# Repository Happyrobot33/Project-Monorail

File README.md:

# Project-Monorail
Project Monorail is an attempt to recreate a design shown by Nicholas Seward (https://www.youtube.com/watch?v=oBBhVcemVHc&amp;t=26s) that uses 1 linear rail to accomplish 3 dimensional movement

Use this to visualize if a point is reachable or not to prevent issues:
https://editor.p5js.org/Happyrobot33/sketches/HqeGeLe6U

https://user-images.githubusercontent.com/32679887/117662900-11516d00-b16e-11eb-9a66-542f85682d6e.mp4

https://user-images.githubusercontent.com/32679887/118267545-3d306380-b48a-11eb-8856-cf8bc8f9db5a.mp4

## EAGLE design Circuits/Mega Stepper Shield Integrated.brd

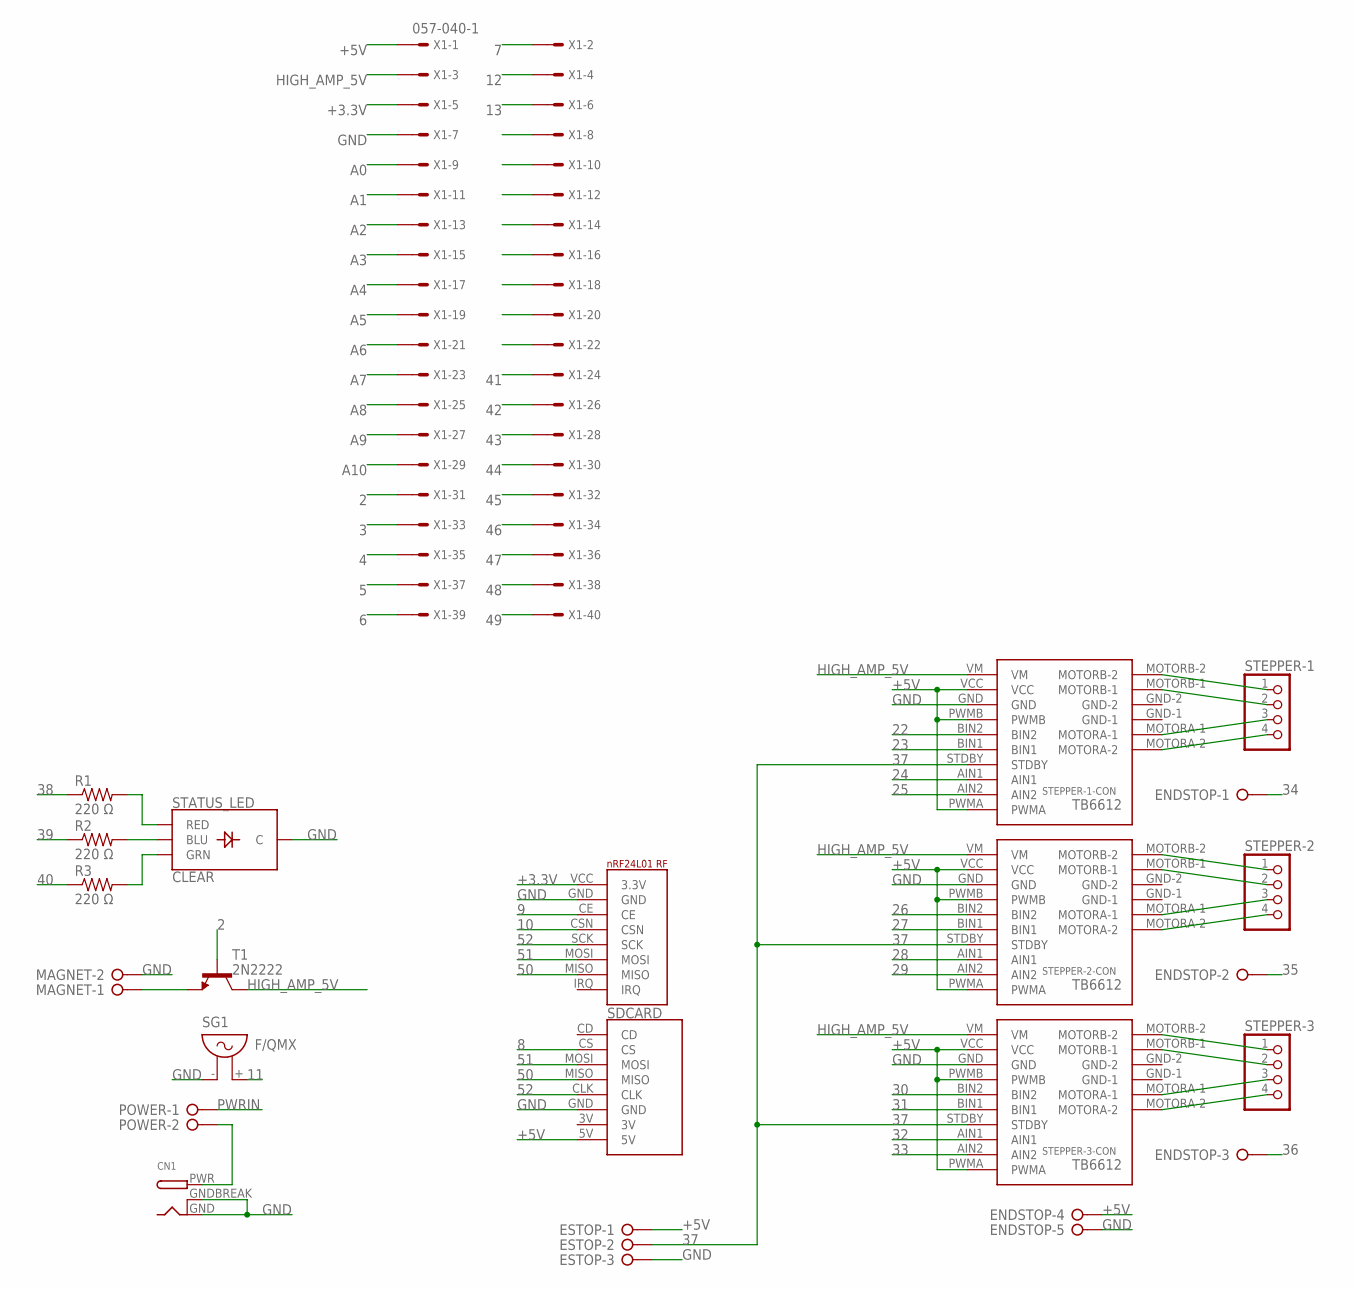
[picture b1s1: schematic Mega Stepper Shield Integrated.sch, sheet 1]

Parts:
CN1: DCBARRELPTH; DCJACK_2MM_PTH
ENDSTOP: W237-05P; W237-5P
ESTOP: W237-3E
MAGNET: W237-02P; W237-132
POWER: W237-02P; W237-132
R1, R2, R3: 220 Ω; 0204/7
SDCARD: MICRO_SD_BREAKOUT; MICROSDCARDBREAKOUT
SG1: F/QMX
STATUS_LED: CLEAR; LED-RGB-THRU
STEPPER-1, STEPPER-2, STEPPER-3: PINHD-1X4; 1X04
STEPPER-1-CON, STEPPER-2-CON, STEPPER-3-CON: TB6612-BREAKOUT-MOTOR-CONTROLLER; TB6612-HEADERS
T1: 2N2222; TO92-EBC-OVAL
U$1: NRF24L01_RF_MODULE; NRF24L01RF
X1: 057-040-1

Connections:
2: T1.B, X1.31; also elsewhere on the board
3: X1.33; also elsewhere on the board
4: X1.35; also elsewhere on the board
5: X1.37; also elsewhere on the board
6: X1.39; also elsewhere on the board
7: X1.2; also elsewhere on the board
8: SDCARD.CS; also elsewhere on the board
9: U$1.CE; also elsewhere on the board
10: U$1.CSN; also elsewhere on the board
11: SG1.+ (2); also elsewhere on the board
12: X1.4; also elsewhere on the board
13: X1.6; also elsewhere on the board
16: X1.8
22: STEPPER-1-CON.BIN2; also elsewhere on the board
23: STEPPER-1-CON.BIN1; also elsewhere on the board
24: STEPPER-1-CON.AIN1; also elsewhere on the board
25: STEPPER-1-CON.AIN2; also elsewhere on the board
26: STEPPER-2-CON.BIN2; also elsewhere on the board
27: STEPPER-2-CON.BIN1; also elsewhere on the board
28: STEPPER-2-CON.AIN1; also elsewhere on the board
29: STEPPER-2-CON.AIN2; also elsewhere on the board
30: STEPPER-3-CON.BIN2; also elsewhere on the board
31: STEPPER-3-CON.BIN1; also elsewhere on the board
32: STEPPER-3-CON.AIN1; also elsewhere on the board
33: STEPPER-3-CON.AIN2; also elsewhere on the board
34: ENDSTOP.1; also elsewhere on the board
35: ENDSTOP.2; also elsewhere on the board
36: ENDSTOP.3; also elsewhere on the board
37: ESTOP.2, STEPPER-1-CON.STDBY, STEPPER-2-CON.STDBY, STEPPER-3-CON.STDBY; also elsewhere on the board
38: R1.1; also elsewhere on the board
39: R2.1; also elsewhere on the board
40: R3.1, X1.22; also elsewhere on the board
41: X1.24; also elsewhere on the board
42: X1.26; also elsewhere on the board
43: X1.28; also elsewhere on the board
44: X1.30; also elsewhere on the board
45: X1.32; also elsewhere on the board
46: X1.34; also elsewhere on the board
47: X1.36; also elsewhere on the board
48: X1.38; also elsewhere on the board
49: X1.40; also elsewhere on the board
50: SDCARD.MISO, U$1.MISO; also elsewhere on the board
51: SDCARD.MOSI, U$1.MOSI; also elsewhere on the board
52: SDCARD.CLK, U$1.SCK; also elsewhere on the board
+3.3V: U$1.VCC (3.3V), X1.5
+5V: ENDSTOP.4, ESTOP.1, SDCARD.5V, STEPPER-1-CON.PWMA, STEPPER-1-CON.PWMB, STEPPER-1-CON.VCC, STEPPER-2-CON.PWMA, STEPPER-2-CON.PWMB, STEPPER-2-CON.VCC, STEPPER-3-CON.PWMA, STEPPER-3-CON.PWMB, STEPPER-3-CON.VCC, X1.1; also elsewhere on the board
A0: X1.9; also elsewhere on the board
A1: X1.11; also elsewhere on the board
A2: X1.13; also elsewhere on the board
A3: X1.15; also elsewhere on the board
A4: X1.17; also elsewhere on the board
A5: X1.19; also elsewhere on the board
A6: X1.21; also elsewhere on the board
A7: X1.23; also elsewhere on the board
A8: X1.25; also elsewhere on the board
A9: X1.27; also elsewhere on the board
A10: X1.29; also elsewhere on the board
GND: CN1.GND, CN1.GNDBREAK, ENDSTOP.5, ESTOP.3, MAGNET.2, SDCARD.GND, SG1.- (1), STATUS_LED.2 (C), STEPPER-1-CON.GND, STEPPER-2-CON.GND, STEPPER-3-CON.GND, U$1.GND, X1.7; also elsewhere on the board
HIGH_AMP_5V: STEPPER-1-CON.VM, STEPPER-2-CON.VM, STEPPER-3-CON.VM, T1.C, X1.3; also elsewhere on the board
unnamed: CN1.PWR, POWER.2
unnamed: STEPPER-1.1, STEPPER-1-CON.MOTORB-2
unnamed: STEPPER-1.2, STEPPER-1-CON.MOTORB-1
unnamed: STEPPER-1.3, STEPPER-1-CON.MOTORA-1
unnamed: STEPPER-1.4, STEPPER-1-CON.MOTORA-2
unnamed: STEPPER-2.1, STEPPER-2-CON.MOTORB-2
unnamed: STEPPER-2.2, STEPPER-2-CON.MOTORB-1
unnamed: STEPPER-2.3, STEPPER-2-CON.MOTORA-1
unnamed: STEPPER-2.4, STEPPER-2-CON.MOTORA-2
unnamed: STEPPER-3.1, STEPPER-3-CON.MOTORB-2
unnamed: STEPPER-3.2, STEPPER-3-CON.MOTORB-1
unnamed: STEPPER-3.3, STEPPER-3-CON.MOTORA-1
unnamed: STEPPER-3.4, STEPPER-3-CON.MOTORA-2
unnamed: R3.2, STATUS_LED.3 (GRN)
unnamed: R2.2, STATUS_LED.4 (BLU)
unnamed: R1.2, STATUS_LED.1 (RED)
unnamed: MAGNET.1, T1.E
PWRIN: POWER.1; also elsewhere on the board

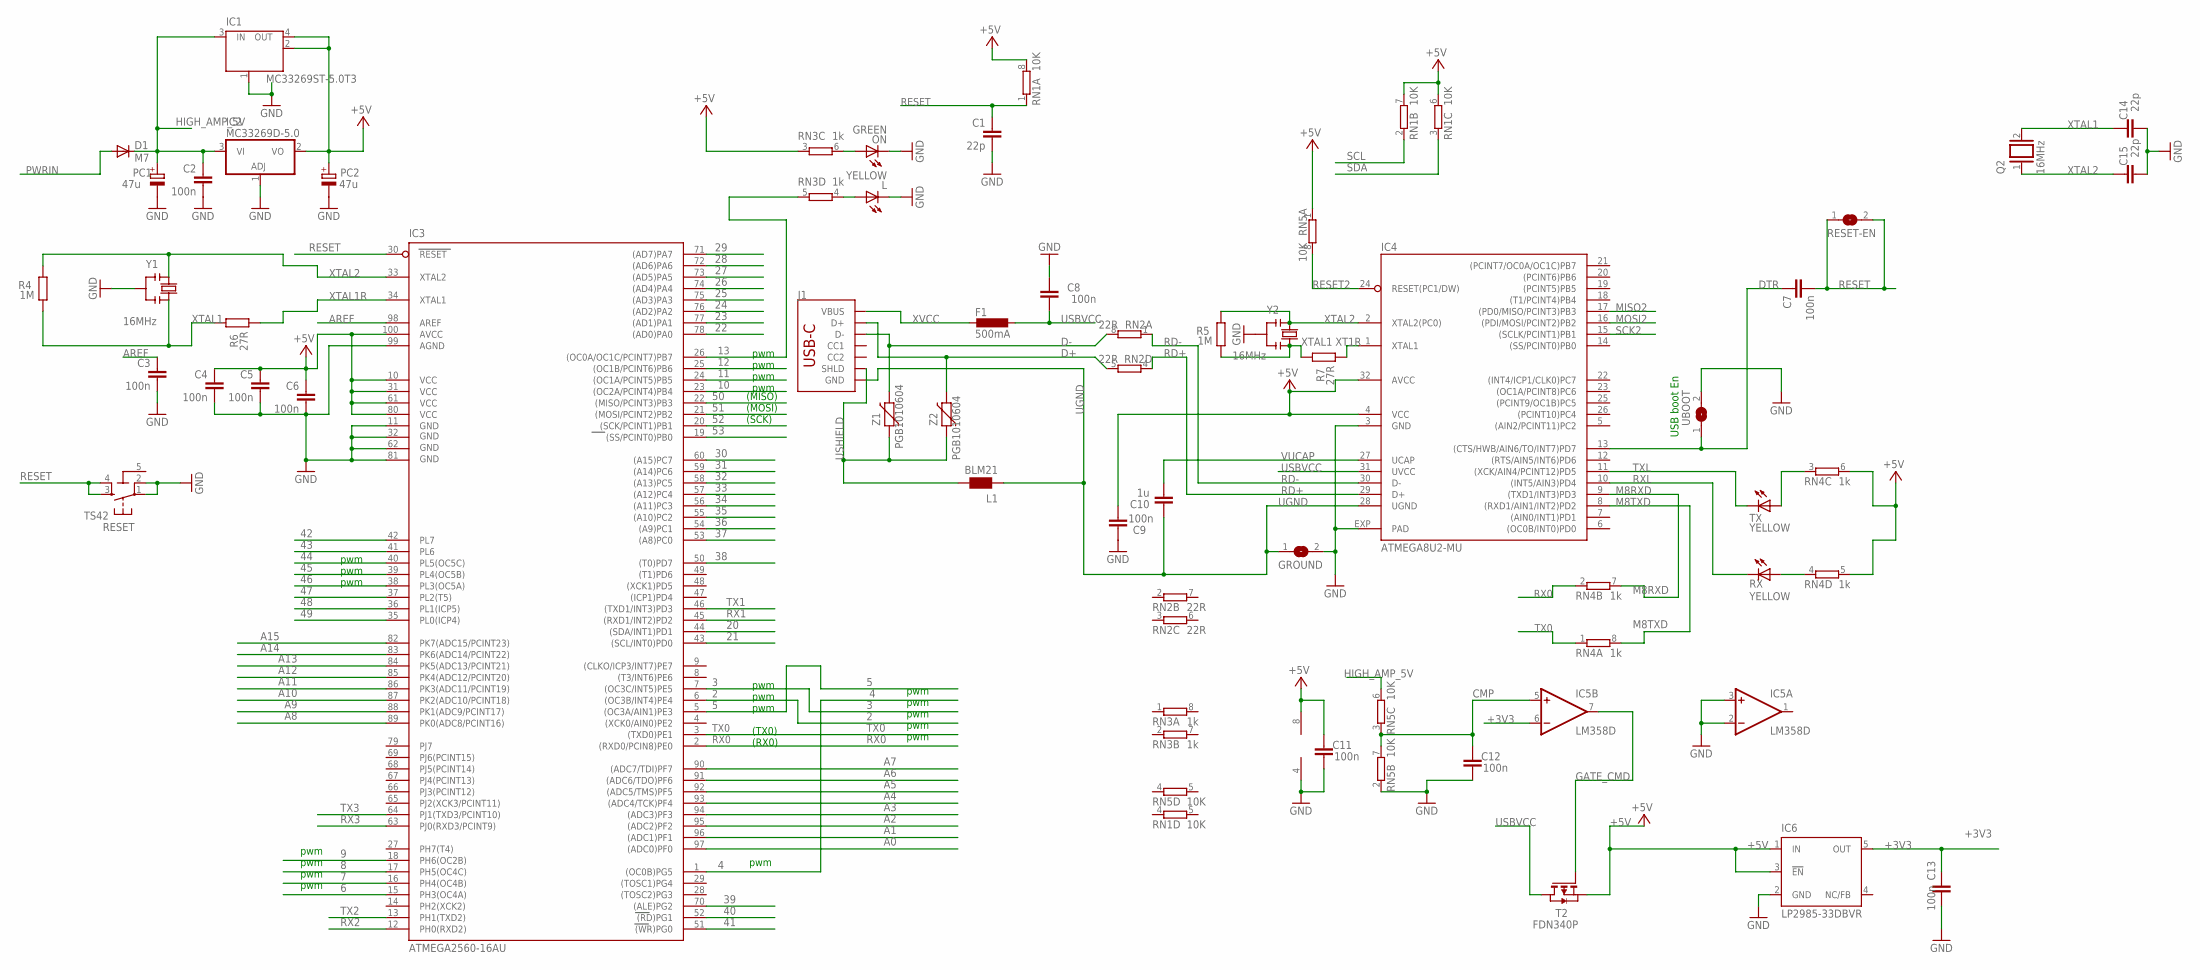
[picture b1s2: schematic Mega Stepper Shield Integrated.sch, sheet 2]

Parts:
C1, C14, C15: 22p; C0603-ROUND
C2, C3, C4, C5, C6, C7, C9, C12, C13: 100n; C0603-ROUND
C8, C11: 100n; C0603
C10: 1u; C0603-ROUND
D1: M7; SMB
F1: 500mA; L1812
GROUND: SJ
IC1: MC33269ST-5.0T3; SOT223
IC2: MC33269D-5.0; DPACK
IC3: ATMEGA2560-16AU; TQFP100
IC4: ATMEGA8U2-MU; QFN32
IC5: LM358D; SO08
IC6: LP2985-33DBVR; SOT23-DBV
J1: USB_C_2-LAYER_PADS; USB-C-16P-2LAYER-PADS
L: YELLOW; CHIP-LED0805
L1: BLM21; 0805
ON: GREEN; CHIP-LED0805
PC1, PC2: 47u; PANASONIC_D
Q2: 16MHz; QS
R4, R5: 1M; R0603-ROUND
R6, R7: 27R; R0603-ROUND
RESET: TS42
RESET-EN: SJ
RN1, RN5: 10K; CAT16
RN2: 22R; CAY16
RN3, RN4: 1k; CAY16
RX: YELLOW; CHIP-LED0805
T2: FDN340P; SOT-23
TX: YELLOW; CHIP-LED0805
UBOOT: SJ
Y1, Y2: 16MHz; RESONATOR
Z1, Z2: PGB1010604; CT/CN0603

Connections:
2: IC3.6 ((OC3B/INT4)PE4); also elsewhere on the board
3: IC3.7 ((OC3C/INT5)PE5); also elsewhere on the board
4: IC3.1 ((OC0B)PG5); also elsewhere on the board
5: IC3.5 ((OC3A/AIN1)PE3); also elsewhere on the board
5-GND: RESET.5 (5-GND)
6: IC3.15 (PH3(OC4A)); also elsewhere on the board
7: IC3.16 (PH4(OC4B)); also elsewhere on the board
8: IC3.17 (PH5(OC4C)); also elsewhere on the board
9: IC3.18 (PH6(OC2B)); also elsewhere on the board
10: IC3.23 ((OC2A/PCINT4)PB4); also elsewhere on the board
11: IC3.24 ((OC1A/PCINT5)PB5); also elsewhere on the board
12: IC3.25 ((OC1B/PCINT6)PB6); also elsewhere on the board
13: IC3.26 ((OC0A/OC1C/PCINT7)PB7), RN3.5 (2); also elsewhere on the board
20: IC3.44 ((SDA/INT1)PD1)
21: IC3.43 ((SCL/INT0)PD0)
22: IC3.78 ((AD0)PA0); also elsewhere on the board
23: IC3.77 ((AD1)PA1); also elsewhere on the board
24: IC3.76 ((AD2)PA2); also elsewhere on the board
25: IC3.75 ((AD3)PA3); also elsewhere on the board
26: IC3.74 ((AD4)PA4); also elsewhere on the board
27: IC3.73 ((AD5)PA5); also elsewhere on the board
28: IC3.72 ((AD6)PA6); also elsewhere on the board
29: IC3.71 ((AD7)PA7); also elsewhere on the board
30: IC3.60 ((A15)PC7); also elsewhere on the board
31: IC3.59 ((A14)PC6); also elsewhere on the board
32: IC3.58 ((A13)PC5); also elsewhere on the board
33: IC3.57 ((A12)PC4); also elsewhere on the board
34: IC3.56 ((A11)PC3); also elsewhere on the board
35: IC3.55 ((A10)PC2); also elsewhere on the board
36: IC3.54 ((A9)PC1); also elsewhere on the board
37: IC3.53 ((A8)PC0); also elsewhere on the board
38: IC3.50 ((T0)PD7); also elsewhere on the board
39: IC3.70 ((ALE)PG2); also elsewhere on the board
40: IC3.52 ((RD)PG1); also elsewhere on the board
41: IC3.51 ((WR)PG0); also elsewhere on the board
42: IC3.42 (PL7); also elsewhere on the board
43: IC3.41 (PL6); also elsewhere on the board
44: IC3.40 (PL5(OC5C)); also elsewhere on the board
45: IC3.39 (PL4(OC5B)); also elsewhere on the board
46: IC3.38 (PL3(OC5A)); also elsewhere on the board
47: IC3.37 (PL2(T5)); also elsewhere on the board
48: IC3.36 (PL1(ICP5)); also elsewhere on the board
49: IC3.35 (PL0(ICP4)); also elsewhere on the board
50: IC3.22 ((MISO/PCINT3)PB3); also elsewhere on the board
51: IC3.21 ((MOSI/PCINT2)PB2); also elsewhere on the board
52: IC3.20 ((SCK/PCINT1)PB1); also elsewhere on the board
53: IC3.19 ((SS/PCINT0)PB0)
+3V3: C13.2, IC5.6 (-IN), IC6.5 (OUT)
+5V: C4.1, C5.1, C6.1, C9.1, C11.2, IC1.2 (OUT), IC1.4 (OUT), IC2.2 (VO), IC3.10 (VCC), IC3.31 (VCC1), IC3.61 (VCC2), IC3.80 (VCC3), IC3.100 (AVCC), IC4.4 (VCC), IC4.32 (AVCC), IC5.8 (V+), IC6.1 (IN), IC6.3 (!EN), PC2.+, RN1.6 (2), RN1.7 (2), RN1.8 (2), RN3.3 (1), RN4.5 (2), RN4.6 (2), RN5.1, T2.2 (S); also elsewhere on the board
A0: IC3.97 ((ADC0)PF0); also elsewhere on the board
A1: IC3.96 ((ADC1)PF1); also elsewhere on the board
A2: IC3.95 ((ADC2)PF2); also elsewhere on the board
A3: IC3.94 ((ADC3)PF3); also elsewhere on the board
A4: IC3.93 ((ADC4/TCK)PF4); also elsewhere on the board
A5: IC3.92 ((ADC5/TMS)PF5); also elsewhere on the board
A6: IC3.91 ((ADC6/TDO)PF6); also elsewhere on the board
A7: IC3.90 ((ADC7/TDI)PF7); also elsewhere on the board
A8: IC3.89 (PK0(ADC8/PCINT16)); also elsewhere on the board
A9: IC3.88 (PK1(ADC9/PCINT17)); also elsewhere on the board
A10: IC3.87 (PK2(ADC10/PCINT18)); also elsewhere on the board
A11: IC3.86 (PK3(ADC11/PCINT19))
A12: IC3.85 (PK4(ADC12/PCINT20))
A13: IC3.84 (PK5(ADC13/PCINT21))
A14: IC3.83 (PK6(ADC14/PCINT22))
A15: IC3.82 (PK7(ADC15/PCINT23))
AREF: C3.1, IC3.98 (AREF)
CMP: C12.2, IC5.5 (+IN), RN5.3 (1), RN5.7 (2)
D+: J1.A6 (D+), J1.B6 (D+), RN2.5 (2), Z2.2
D-: J1.A7 (D-), J1.B7 (D-), RN2.8 (2), Z1.2
DTR: C7.1, IC4.13 ((CTS/HWB/AIN6/TO/INT7)PD7), UBOOT.1
GATE_CMD: IC5.7 (OUT), T2.3 (G)
GND: C1.2, C2.2, C3.2, C4.2, C5.2, C6.2, C8.2, C9.2, C11.1, C12.1, C13.1, C14.1, C15.1, GROUND.2, IC1.1 (GND/ADJ), IC2.1 (ADJ), IC3.11 (GND), IC3.32 (GND1), IC3.62 (GND2), IC3.81 (GND3), IC3.99 (AGND), IC4.3 (GND), IC4.EXP (PAD), IC5.2 (-IN), IC5.3 (+IN), IC5.4 (V-), IC6.2 (GND), L.C, ON.C, PC1.-, PC2.-, RESET.1, RESET.2, RN5.2 (1), UBOOT.2, Y1.2, Y2.2; also elsewhere on the board
HIGH_AMP_5V: C2.1, D1.C, IC1.3 (IN), IC2.3 (VI), PC1.+, RN5.6 (2); also elsewhere on the board
M8RXD: IC4.9 ((TXD1/INT3)PD3), RN4.7 (2)
M8TXD: IC4.8 ((RXD1/AIN1/INT2)PD2), RN4.8 (2)
MISO2: IC4.17 ((PD0/MISO/PCINT3)PB3)
MOSI2: IC4.16 ((PDI/MOSI/PCINT2)PB2)
unnamed: ON.A, RN3.6 (2)
unnamed: L.A, RN3.4 (1)
unnamed: RN4.4 (1), RX.A
unnamed: RN4.3 (1), TX.A
PWRIN: D1.A; also elsewhere on the board
RD+: IC4.29 (D+), RN2.4 (1)
RD-: IC4.30 (D-), RN2.1
RESET: C1.1, C7.2, IC3.30 (RESET), RESET.3, RESET.4, RESET-EN.1, RESET-EN.2, RN1.1
RESET2: IC4.24 (RESET(PC1/DW)), RN5.8 (2)
RX0: IC3.2 ((RXD0/PCIN8)PE0), RN4.2 (1)
RX1: IC3.45 ((RXD1/INT2)PD2)
RX2: IC3.12 (PH0(RXD2))
RX3: IC3.63 (PJ0(RXD3/PCINT9))
RXL: IC4.10 ((INT5/AIN3)PD4), RX.C
SCK2: IC4.15 ((SCLK/PCINT1)PB1)
SCL: RN1.2 (1)
SDA: RN1.3 (1)
TX0: IC3.3 ((TXD0)PE1), RN4.1
TX1: IC3.46 ((TXD1/INT3)PD3)
TX2: IC3.13 (PH1(TXD2))
TX3: IC3.64 (PJ1(TXD3/PCINT10))
TXL: IC4.11 ((XCK/AIN4/PCINT12)PD5), TX.C
UGND: C10.2, GROUND.1, IC4.28 (UGND), J1.GND, J1.GND2 (GND), L1.1
USBVCC: C8.1, F1.1, IC4.31 (UVCC), T2.1 (D)
USHIELD: J1.SHLD1 (SHLD), J1.SHLD2 (SHLD), J1.SHLD3 (SHLD), J1.SHLD4 (SHLD), L1.2, Z1.1, Z2.1
VUCAP: C10.1, IC4.27 (UCAP)
XT1R: IC4.1 (XTAL1), R7.1
XTAL1: C14.2, Q2.2, R4.1, R5.1, R6.2, R7.2, Y1.3, Y2.3
XTAL1R: IC3.34 (XTAL1), R6.1
XTAL2: C15.2, IC3.33 (XTAL2), IC4.2 (XTAL2(PC0)), Q2.1, R4.2, R5.2, Y1.1, Y2.1
XVCC: F1.2, J1.VBUS1 (VBUS), J1.VBUS2 (VBUS)

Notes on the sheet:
pwm
(TX0)
(RX0)
(MISO)
(SCK)
(MOSI)
USB boot En

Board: 2 copper layers, 70 parts (0 on the bottom side), 106 nets, no tracks yet.

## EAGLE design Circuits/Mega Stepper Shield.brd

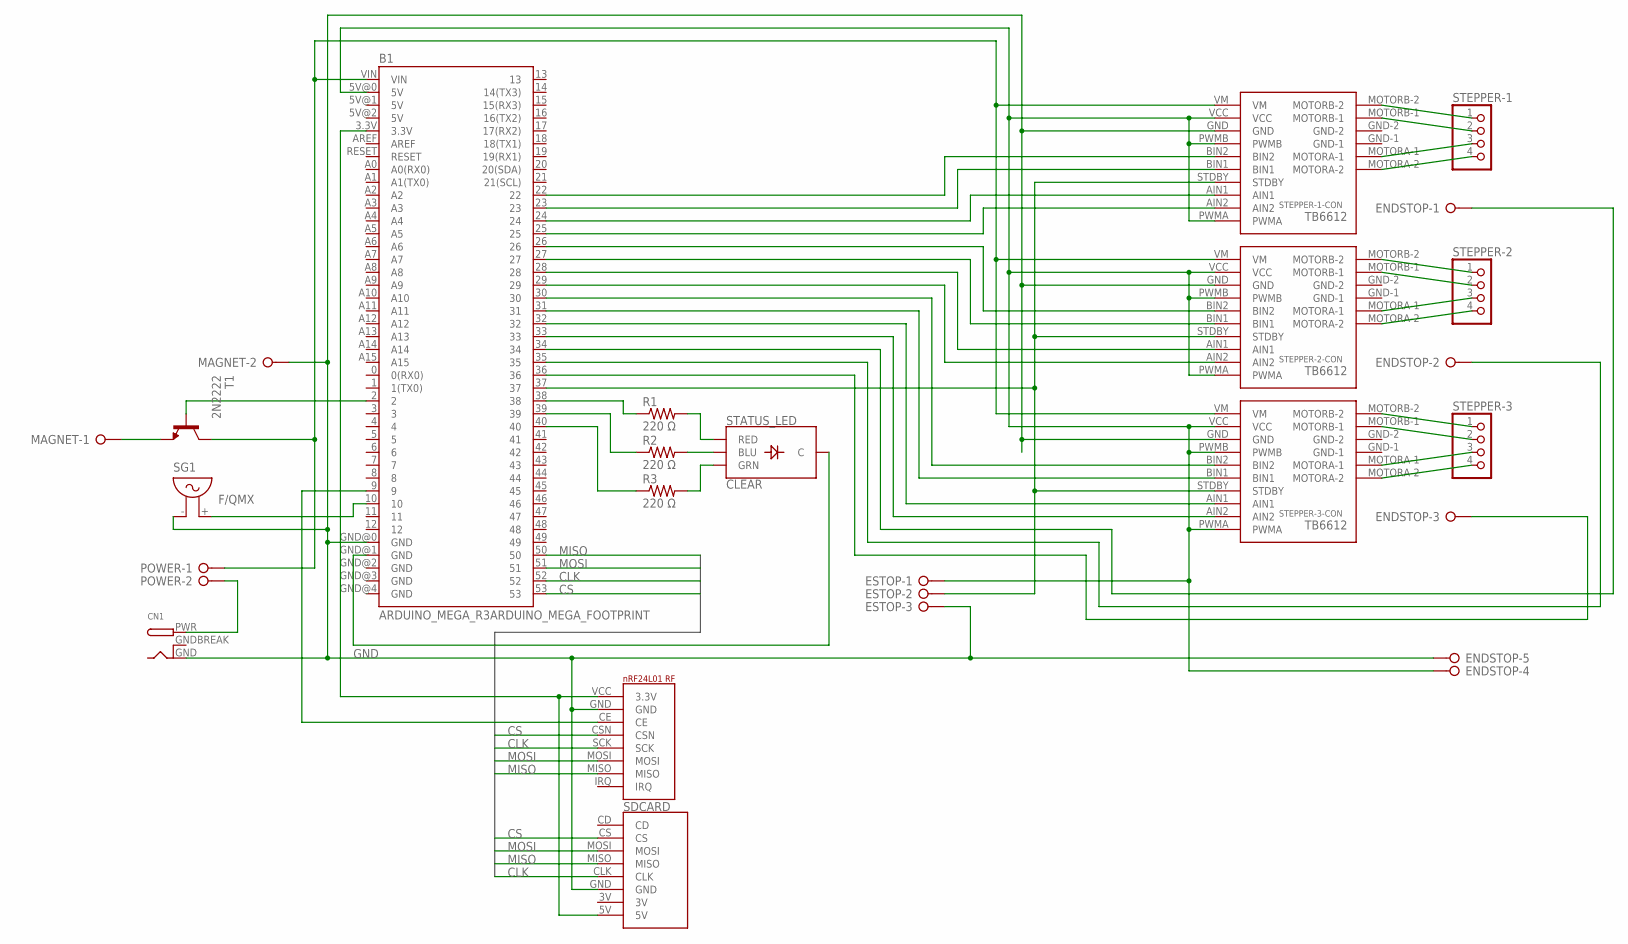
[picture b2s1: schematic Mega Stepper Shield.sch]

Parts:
B1: ARDUINO_MEGA_R3ARDUINO_MEGA_FOOTPRINT; ARDUINO_MEGA_SHIELD_DIMENSIONLESS
CN1: DCBARRELPTH; DCJACK_2MM_PTH
ENDSTOP: W237-05P; W237-5P
ESTOP: W237-3E
MAGNET: W237-02P; W237-132
POWER: W237-02P; W237-132
R1, R2, R3: 220 Ω; 0204/7
SDCARD: MICRO_SD_BREAKOUT; MICROSDCARDBREAKOUT
SG1: F/QMX
STATUS_LED: CLEAR; LED-RGB-THRU
STEPPER-1, STEPPER-2, STEPPER-3: PINHD-1X4; 1X04
STEPPER-1-CON, STEPPER-2-CON, STEPPER-3-CON: TB6612-BREAKOUT-MOTOR-CONTROLLER; TB6612-HEADERS
T1: 2N2222; TO92-EBC-OVAL
U$1: NRF24L01_RF_MODULE; NRF24L01RF

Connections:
3.3V: B1.3.3V, SDCARD.5V, U$1.VCC (3.3V)
5V: B1.5V@0 (5V), ENDSTOP.4, ESTOP.1, STEPPER-1-CON.PWMA, STEPPER-1-CON.PWMB, STEPPER-1-CON.VCC, STEPPER-2-CON.PWMA, STEPPER-2-CON.PWMB, STEPPER-2-CON.VCC, STEPPER-3-CON.PWMA, STEPPER-3-CON.PWMB, STEPPER-3-CON.VCC
12V10A: B1.VIN, POWER.1, STEPPER-1-CON.VM, STEPPER-2-CON.VM, STEPPER-3-CON.VM, T1.C
AIN1: B1.24, STEPPER-1-CON.AIN1
AIN2: B1.25, STEPPER-1-CON.AIN2
BIN2: B1.22, STEPPER-1-CON.BIN2
CLK: B1.52, SDCARD.CLK, U$1.SCK
CS: B1.53, SDCARD.CS, U$1.CSN
GND: B1.GND@0 (GND), CN1.GND, ENDSTOP.5, ESTOP.3, MAGNET.2, SDCARD.GND, SG1.- (1), STEPPER-1-CON.GND, STEPPER-2-CON.GND, STEPPER-3-CON.GND, U$1.GND
GNDBREAK: CN1.GNDBREAK
MISO: B1.50, SDCARD.MISO, U$1.MISO
MOSI: B1.51, SDCARD.MOSI, U$1.MOSI
unnamed: B1.36, ENDSTOP.3
unnamed: B1.10, SG1.+ (2)
unnamed: B1.30, STEPPER-3-CON.BIN2
unnamed: B1.26, STEPPER-2-CON.BIN2
unnamed: B1.27, STEPPER-2-CON.BIN1
unnamed: B1.28, STEPPER-2-CON.AIN1
unnamed: B1.29, STEPPER-2-CON.AIN2
unnamed: B1.31, STEPPER-3-CON.BIN1
unnamed: B1.32, STEPPER-3-CON.AIN1
unnamed: B1.33, STEPPER-3-CON.AIN2
unnamed: CN1.PWR, POWER.2
unnamed: B1.35, ENDSTOP.2
unnamed: B1.37, ESTOP.2, STEPPER-1-CON.STDBY, STEPPER-2-CON.STDBY, STEPPER-3-CON.STDBY
unnamed: B1.34, ENDSTOP.1
unnamed: STEPPER-1.1, STEPPER-1-CON.MOTORB-2
unnamed: STEPPER-1.2, STEPPER-1-CON.MOTORB-1
unnamed: STEPPER-1.3, STEPPER-1-CON.MOTORA-1
unnamed: STEPPER-1.4, STEPPER-1-CON.MOTORA-2
unnamed: STEPPER-2.1, STEPPER-2-CON.MOTORB-2
unnamed: STEPPER-2.2, STEPPER-2-CON.MOTORB-1
unnamed: STEPPER-2.3, STEPPER-2-CON.MOTORA-1
unnamed: STEPPER-2.4, STEPPER-2-CON.MOTORA-2
unnamed: STEPPER-3.1, STEPPER-3-CON.MOTORB-2
unnamed: STEPPER-3.2, STEPPER-3-CON.MOTORB-1
unnamed: STEPPER-3.3, STEPPER-3-CON.MOTORA-1
unnamed: STEPPER-3.4, STEPPER-3-CON.MOTORA-2
unnamed: B1.23, STEPPER-1-CON.BIN1
unnamed: R3.2, STATUS_LED.3 (GRN)
unnamed: R2.2, STATUS_LED.4 (BLU)
unnamed: R1.2, STATUS_LED.1 (RED)
unnamed: B1.GND@1 (GND), STATUS_LED.2 (C)
unnamed: B1.9, U$1.CE
unnamed: B1.38, R1.1
unnamed: B1.39, R2.1
unnamed: B1.40, R3.1
unnamed: B1.2, T1.B
unnamed: MAGNET.1, T1.E

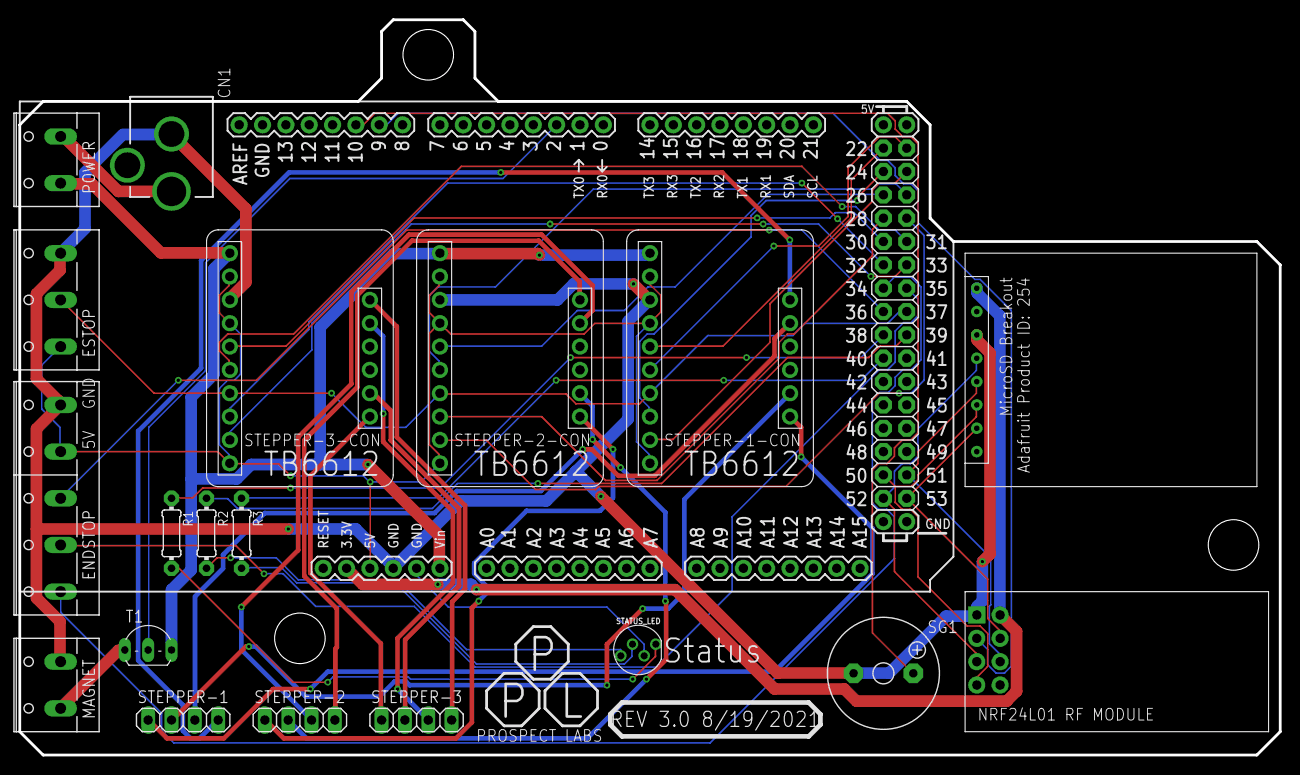
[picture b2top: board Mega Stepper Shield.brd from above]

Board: 2 copper layers, 137.2 x 80.0 mm, 20 parts (0 on the bottom side), 48 nets.

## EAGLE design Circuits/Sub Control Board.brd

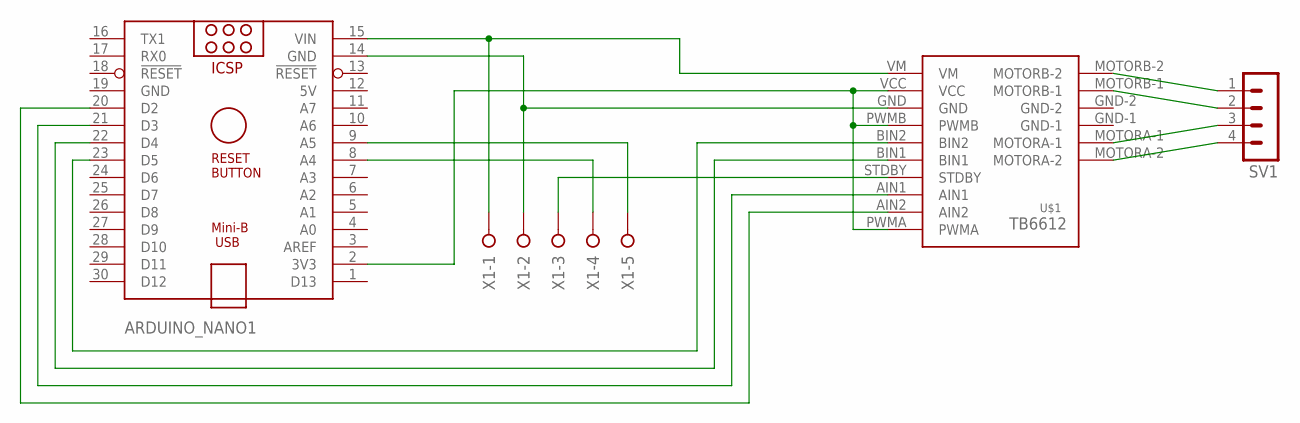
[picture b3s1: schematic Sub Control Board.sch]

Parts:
ARDUINO_NANO1: ARDUINO_NANO
SV1: MA04-1
U$1: TB6612-BREAKOUT-MOTOR-CONTROLLER; TB6612-HEADERS
X1: W237-05P; W237-5P

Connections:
5V: ARDUINO_NANO1.12 (5V)
GND: ARDUINO_NANO1.19 (GND)
unnamed: ARDUINO_NANO1.15 (VIN), U$1.VM, X1.1
unnamed: ARDUINO_NANO1.14 (GND), U$1.GND, X1.2
unnamed: U$1.STDBY, X1.3
unnamed: ARDUINO_NANO1.8 (A4), X1.4
unnamed: ARDUINO_NANO1.9 (A5), X1.5
unnamed: ARDUINO_NANO1.2 (3V3), U$1.PWMA, U$1.PWMB, U$1.VCC
unnamed: ARDUINO_NANO1.23 (D5), U$1.BIN2
unnamed: ARDUINO_NANO1.22 (D4), U$1.BIN1
unnamed: ARDUINO_NANO1.21 (D3), U$1.AIN1
unnamed: ARDUINO_NANO1.20 (D2), U$1.AIN2
unnamed: SV1.1, U$1.MOTORB-2
unnamed: SV1.2, U$1.MOTORB-1
unnamed: SV1.3, U$1.MOTORA-1
unnamed: SV1.4, U$1.MOTORA-2

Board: 2 copper layers, 4 parts (0 on the bottom side), 14 nets, no tracks yet.

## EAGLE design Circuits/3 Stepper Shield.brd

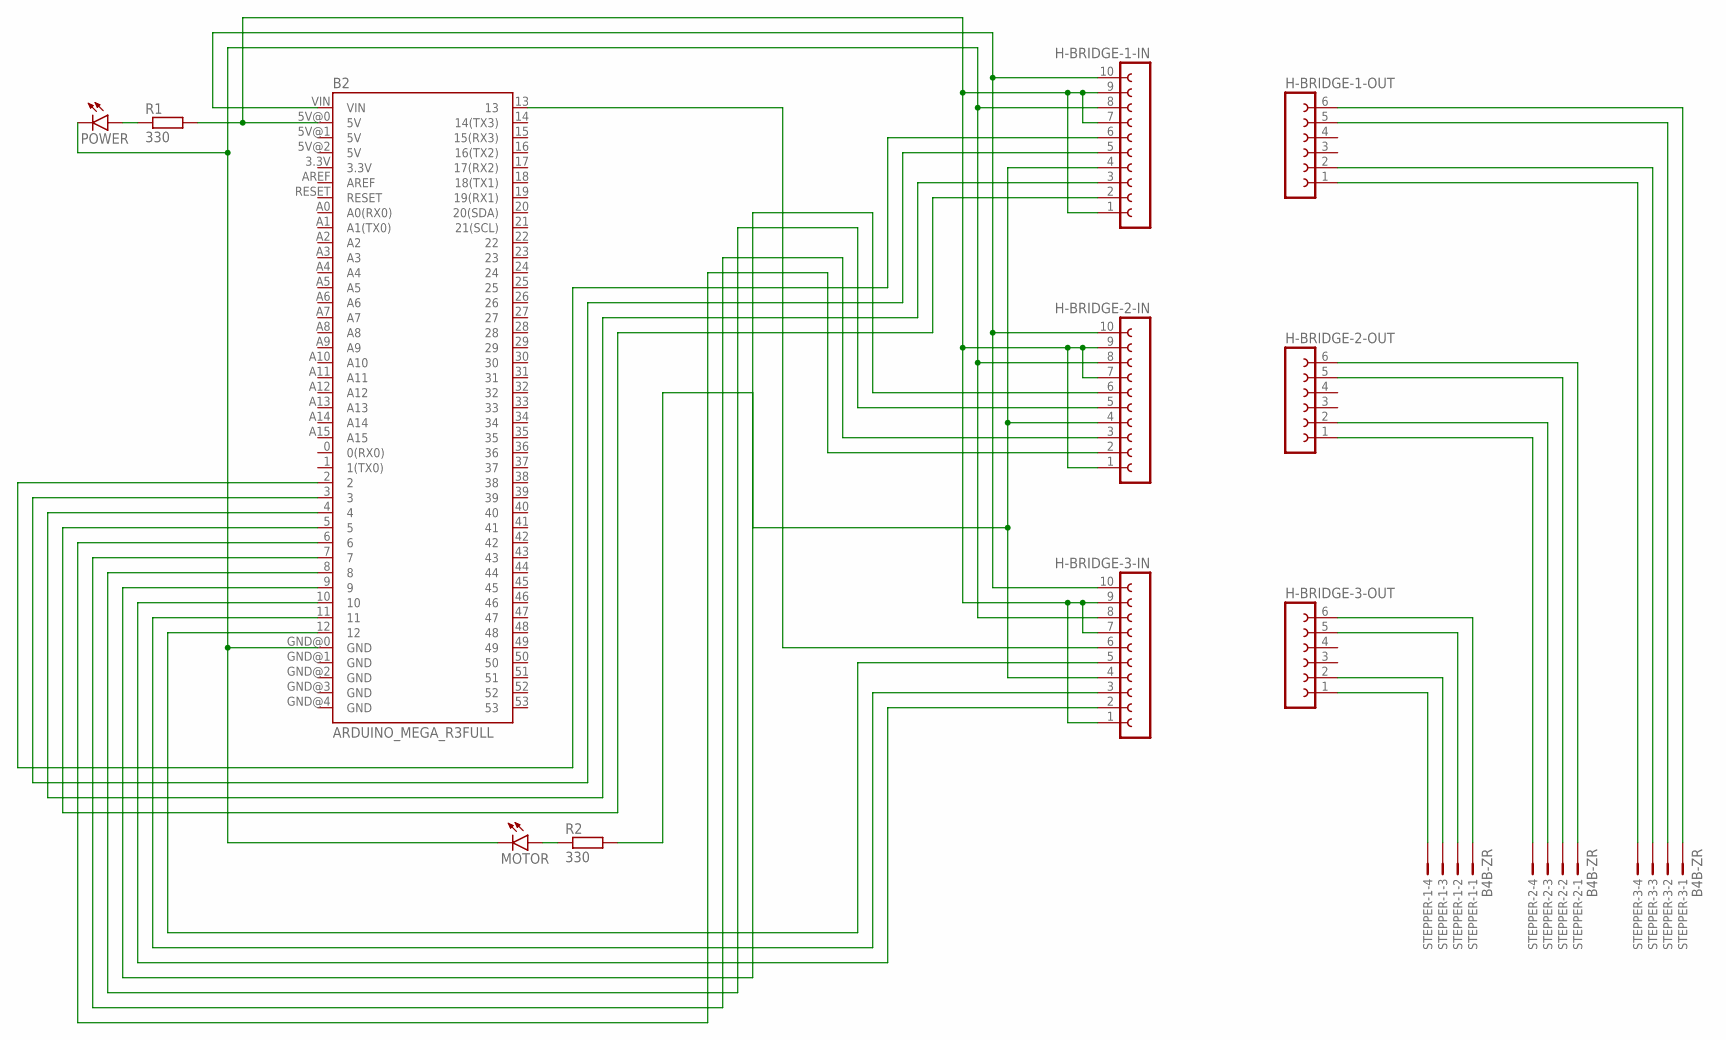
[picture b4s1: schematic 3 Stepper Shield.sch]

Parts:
B2: ARDUINO_MEGA_R3FULL; ARDUINO_MEGA
H-BRIDGE-1-IN, H-BRIDGE-2-IN, H-BRIDGE-3-IN: FE10-1; FE10
H-BRIDGE-1-OUT, H-BRIDGE-2-OUT, H-BRIDGE-3-OUT: FE06-1; FE06
MOTOR: LED5MM
POWER: LED5MM
R1, R2: 330; 0207/10
STEPPER-1, STEPPER-2, STEPPER-3: B4B-ZR

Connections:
unnamed: B2.5, H-BRIDGE-1-IN.2
unnamed: B2.4, H-BRIDGE-1-IN.3
unnamed: B2.3, H-BRIDGE-1-IN.5
unnamed: B2.2, H-BRIDGE-1-IN.6
unnamed: B2.9, H-BRIDGE-2-IN.6
unnamed: B2.8, H-BRIDGE-2-IN.5
unnamed: B2.7, H-BRIDGE-2-IN.3
unnamed: B2.6, H-BRIDGE-2-IN.2
unnamed: B2.13, H-BRIDGE-3-IN.6
unnamed: B2.12, H-BRIDGE-3-IN.5
unnamed: B2.11, H-BRIDGE-3-IN.3
unnamed: B2.10, H-BRIDGE-3-IN.2
unnamed: B2.VIN, H-BRIDGE-1-IN.10, H-BRIDGE-2-IN.10, H-BRIDGE-3-IN.10
unnamed: B2.GND@0 (GND), H-BRIDGE-1-IN.8, H-BRIDGE-2-IN.8, H-BRIDGE-3-IN.8, MOTOR.K (C), POWER.K (C)
unnamed: B2.5V@0 (5V), H-BRIDGE-1-IN.1, H-BRIDGE-1-IN.7, H-BRIDGE-1-IN.9, H-BRIDGE-2-IN.1, H-BRIDGE-2-IN.7, H-BRIDGE-2-IN.9, H-BRIDGE-3-IN.1, H-BRIDGE-3-IN.7, H-BRIDGE-3-IN.9, R1.2
unnamed: MOTOR.A, R2.1
unnamed: H-BRIDGE-1-IN.4, H-BRIDGE-2-IN.4, H-BRIDGE-3-IN.4, R2.2
unnamed: H-BRIDGE-3-OUT.6, STEPPER-1.1
unnamed: H-BRIDGE-3-OUT.5, STEPPER-1.2
unnamed: H-BRIDGE-3-OUT.2, STEPPER-1.3
unnamed: H-BRIDGE-3-OUT.1, STEPPER-1.4
unnamed: H-BRIDGE-2-OUT.1, STEPPER-2.4
unnamed: H-BRIDGE-2-OUT.2, STEPPER-2.3
unnamed: H-BRIDGE-2-OUT.5, STEPPER-2.2
unnamed: H-BRIDGE-2-OUT.6, STEPPER-2.1
unnamed: H-BRIDGE-1-OUT.1, STEPPER-3.4
unnamed: H-BRIDGE-1-OUT.2, STEPPER-3.3
unnamed: H-BRIDGE-1-OUT.5, STEPPER-3.2
unnamed: H-BRIDGE-1-OUT.6, STEPPER-3.1
unnamed: POWER.A, R1.1

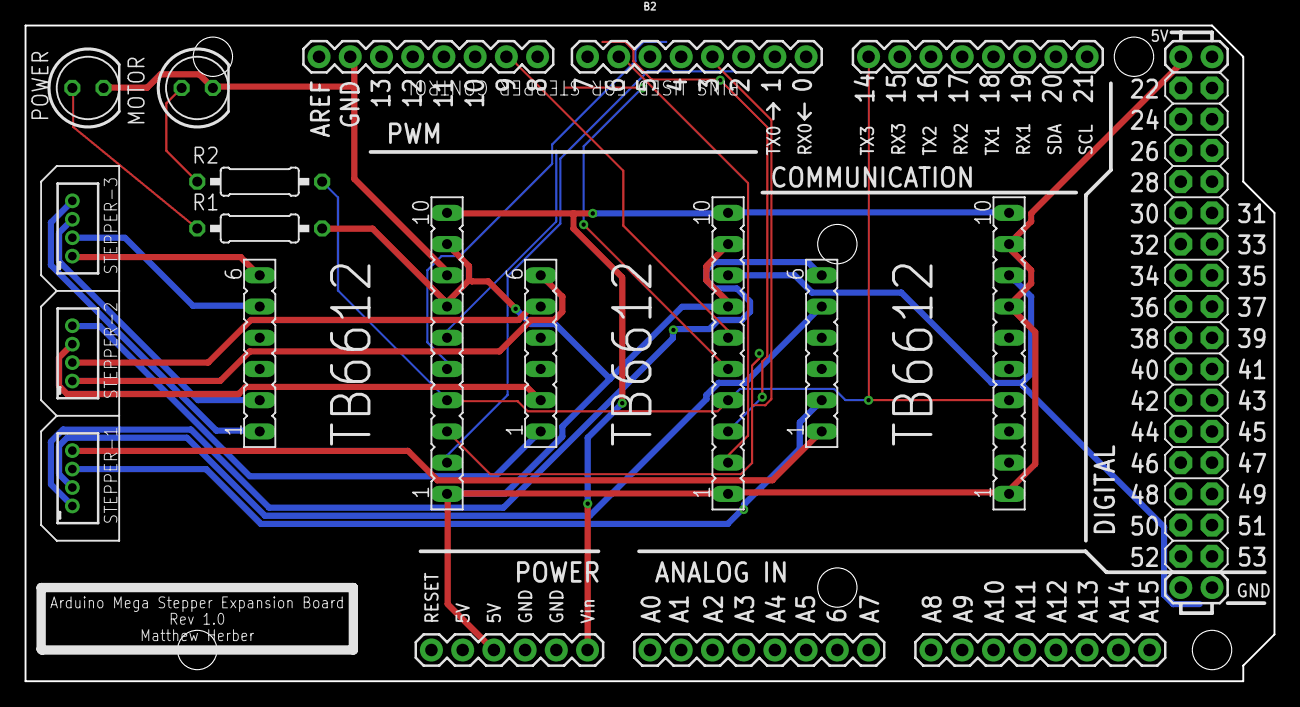
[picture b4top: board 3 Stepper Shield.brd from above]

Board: 2 copper layers, 101.6 x 53.3 mm, 14 parts (0 on the bottom side), 30 nets.

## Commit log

2021-05-04 Initial commit including current source code
2021-05-04 Commit to sync to HDD
    Added CAD and circuit board schematic
2021-05-04 Re Organization of file structure
2021-05-04 Fixed arduino sketchbook
2021-05-04 Add new commands and more comments
    Added accel and speed command, aswell as support for comments using #
2021-05-04 Segmented debug program
2021-05-04 Changed to correct EAGLE files from laptop
2021-05-04 added header comment
2021-05-04 Update code to hopefully have the right MM to Step number
2021-05-04 new ratio
2021-05-04 Update Drive gear to have D shaft
2021-05-04 Updated Code and Model
2021-05-06 Edited Gear Rack to include mounting holes
2021-05-07 Fixed Discrepancy between purchased parts and cad
    Also redid the slide casings to work and be simple in order for testing
2021-05-07 Add alternative smaller spur gear incase torque is an issue
2021-05-08 Temporary Rack mount
2021-05-09 Changed for repeatability testing
2021-05-10 Managed to create an engineering render
    Calculates the positions, the only thing missing is the arms themselves, as that would require bones and IK
2021-05-10 Added Engineering render to readme
2021-05-10 Closed file lol
    Should really do that next time before commiting
2021-05-10 Added calculation to make steppers all arrive at the same time
2021-05-10 Slowed down due to mechanical instability causing skipped steps
    This isnt an issue when finished (atleast to my knowledge) as when this is built correctly it will be using screws, not zipties. the zipties are allowing it to resonate quite badly
2021-05-12 slight changes to model
2021-05-12 Update stored Program and flipped drive direction
2021-05-13 Tweaked MM ratio, added L and J moves and fixed bug with linear move code
2021-05-14 Added Arc commands, and implemented a new way to interpret command values
2021-05-14 Bearing Fit test files
2021-05-14 Arc commands Depreciated for now as they do not function
    Come back to later. unsure why broke
2021-05-14 Fixed bug with stepper 2 location.
    Was sending in degrees into tan() when the format should be radians
2021-05-14 comment reword
2021-05-14 Add circle move to readme
2021-05-14 Update Blender scene to reflect Circle Animation
2021-05-14 Add gitattributes to fix the repo showing up as majority Prolog
2021-05-14 Add Circuits to gitattributes
2021-05-14 Add every folder that shouldnt contain code to gitattributes
2021-05-14 Clean up code format
2021-05-15 Fixed Arc Commands and overall stability improvements
2021-05-15 Edit to stored program
2021-05-16 bearing design for bar and improvements to head file
2021-05-16 Updated Head part to include bearings, and reduced weight
2021-05-17 Attempted improvements to bars and fixed head
2021-05-18 create a split version of the arms
2021-05-18 Add generated STL files
2021-05-18 Try out new gitattributes
2021-08-06 Update CAD and Program
    Added EOAT commands
    Added stand to CAD
2021-08-11 Buncha Code Fixes
    Fixed negative MM step value
    Added error out on negative stepper positions
    Zeroing now offsets after endstop hit
2021-08-17 Add position visualizer / checker
2021-08-20 Update CAD
2021-08-21 add required library
2021-08-21 Update schematic and prototype schematic
    Added RF module to schematic, created a prototype sub board for multiple stepper control
2021-08-21 Add Light Stack and CAD Materials
    Added custom lightstack and custom materials to fix the density of printed parts. Also cleaned up the main assembly tree into folders
2021-08-23 Update Board Design
2021-08-26 Update Board
    Added SPI Bus, changed symbol for SD Card Breakout, changed board layout
2021-08-27 Update Circuit and include electrical mount
2021-08-28 Changes to improve Flexibility
2021-08-31 Create Integrated Version of Board
2021-08-31 Improve CAD to reduce Backlash
2021-08-31 Tool Changer Mockup
2021-11-01 Re Added Non integrated board design
    Realized I removed these when updating the boards to an integrated version
2021-12-17 Redesign 4.0
    Change Carts to cut plates
    Change motion to bearing solution from bushings
    lots of other fixes
2021-12-17 Remove Smart Fasteners
    Smart Fasteners werent coming in right on a different machine
2021-12-17 Change layout of bearings to half count
2021-12-17 Fix folder structure and part naming
2021-12-17 remove unneccesary processing folder/files
2021-12-17 Add readme badges
2021-12-17 Fix Git Ignore and update Materials
2021-12-17 Fix Gear Rack Height
2021-12-17 Fix Cart Endstop Peg Height
2021-12-17 Update Hex Size and insert hex hardware
    Not fully done with this commit-TBF
2021-12-20 Sync Files from laptop
    Missed brd changes and code changes for speed
2022-10-03 Redesign to use thrust bearings
2022-10-03 closed solidworks
2022-10-17 Fix gitignore and missing bearings
2022-10-17 save changes
2022-10-21 Move gear rack to back, with proper mounting solution
2022-10-21 merge
2023-05-22 Redesign to move stepper mounts to new gear rack position

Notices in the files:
parts and their libraries:
SparkFun-Boards: Licensing: Creative Commons ShareAlike 4.0 International - https://creativecommons.org/licenses/by-sa/4.0
